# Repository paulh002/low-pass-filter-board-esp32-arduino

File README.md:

# low-pass-filter-board-esp32-arduino
Lowpass filter board managed by ESP32

Low pass filter for RF amp managed by ESP32 VFO or RF Amp / SWR meter (also ESP32).
I use the same PCB as the VFO as controler but do not install the VFO components like si5351. The LPF can be direct managed from VFO software or stand alone with SWR / RFAMP software, from Loftur Jonasson, TF3LJ / VE2LJX (PSWR_T software). I made an adaption of this software for ESP32 and Adafruit 2.8 display. But I am not completly happy with it. Because it uses fixed spaced fonts which are not available in adafruit library. But for now it works with some GUI bugs which I still need to fix.

Here the LPF build in into my tranceiver and managed by esp32 VFO.

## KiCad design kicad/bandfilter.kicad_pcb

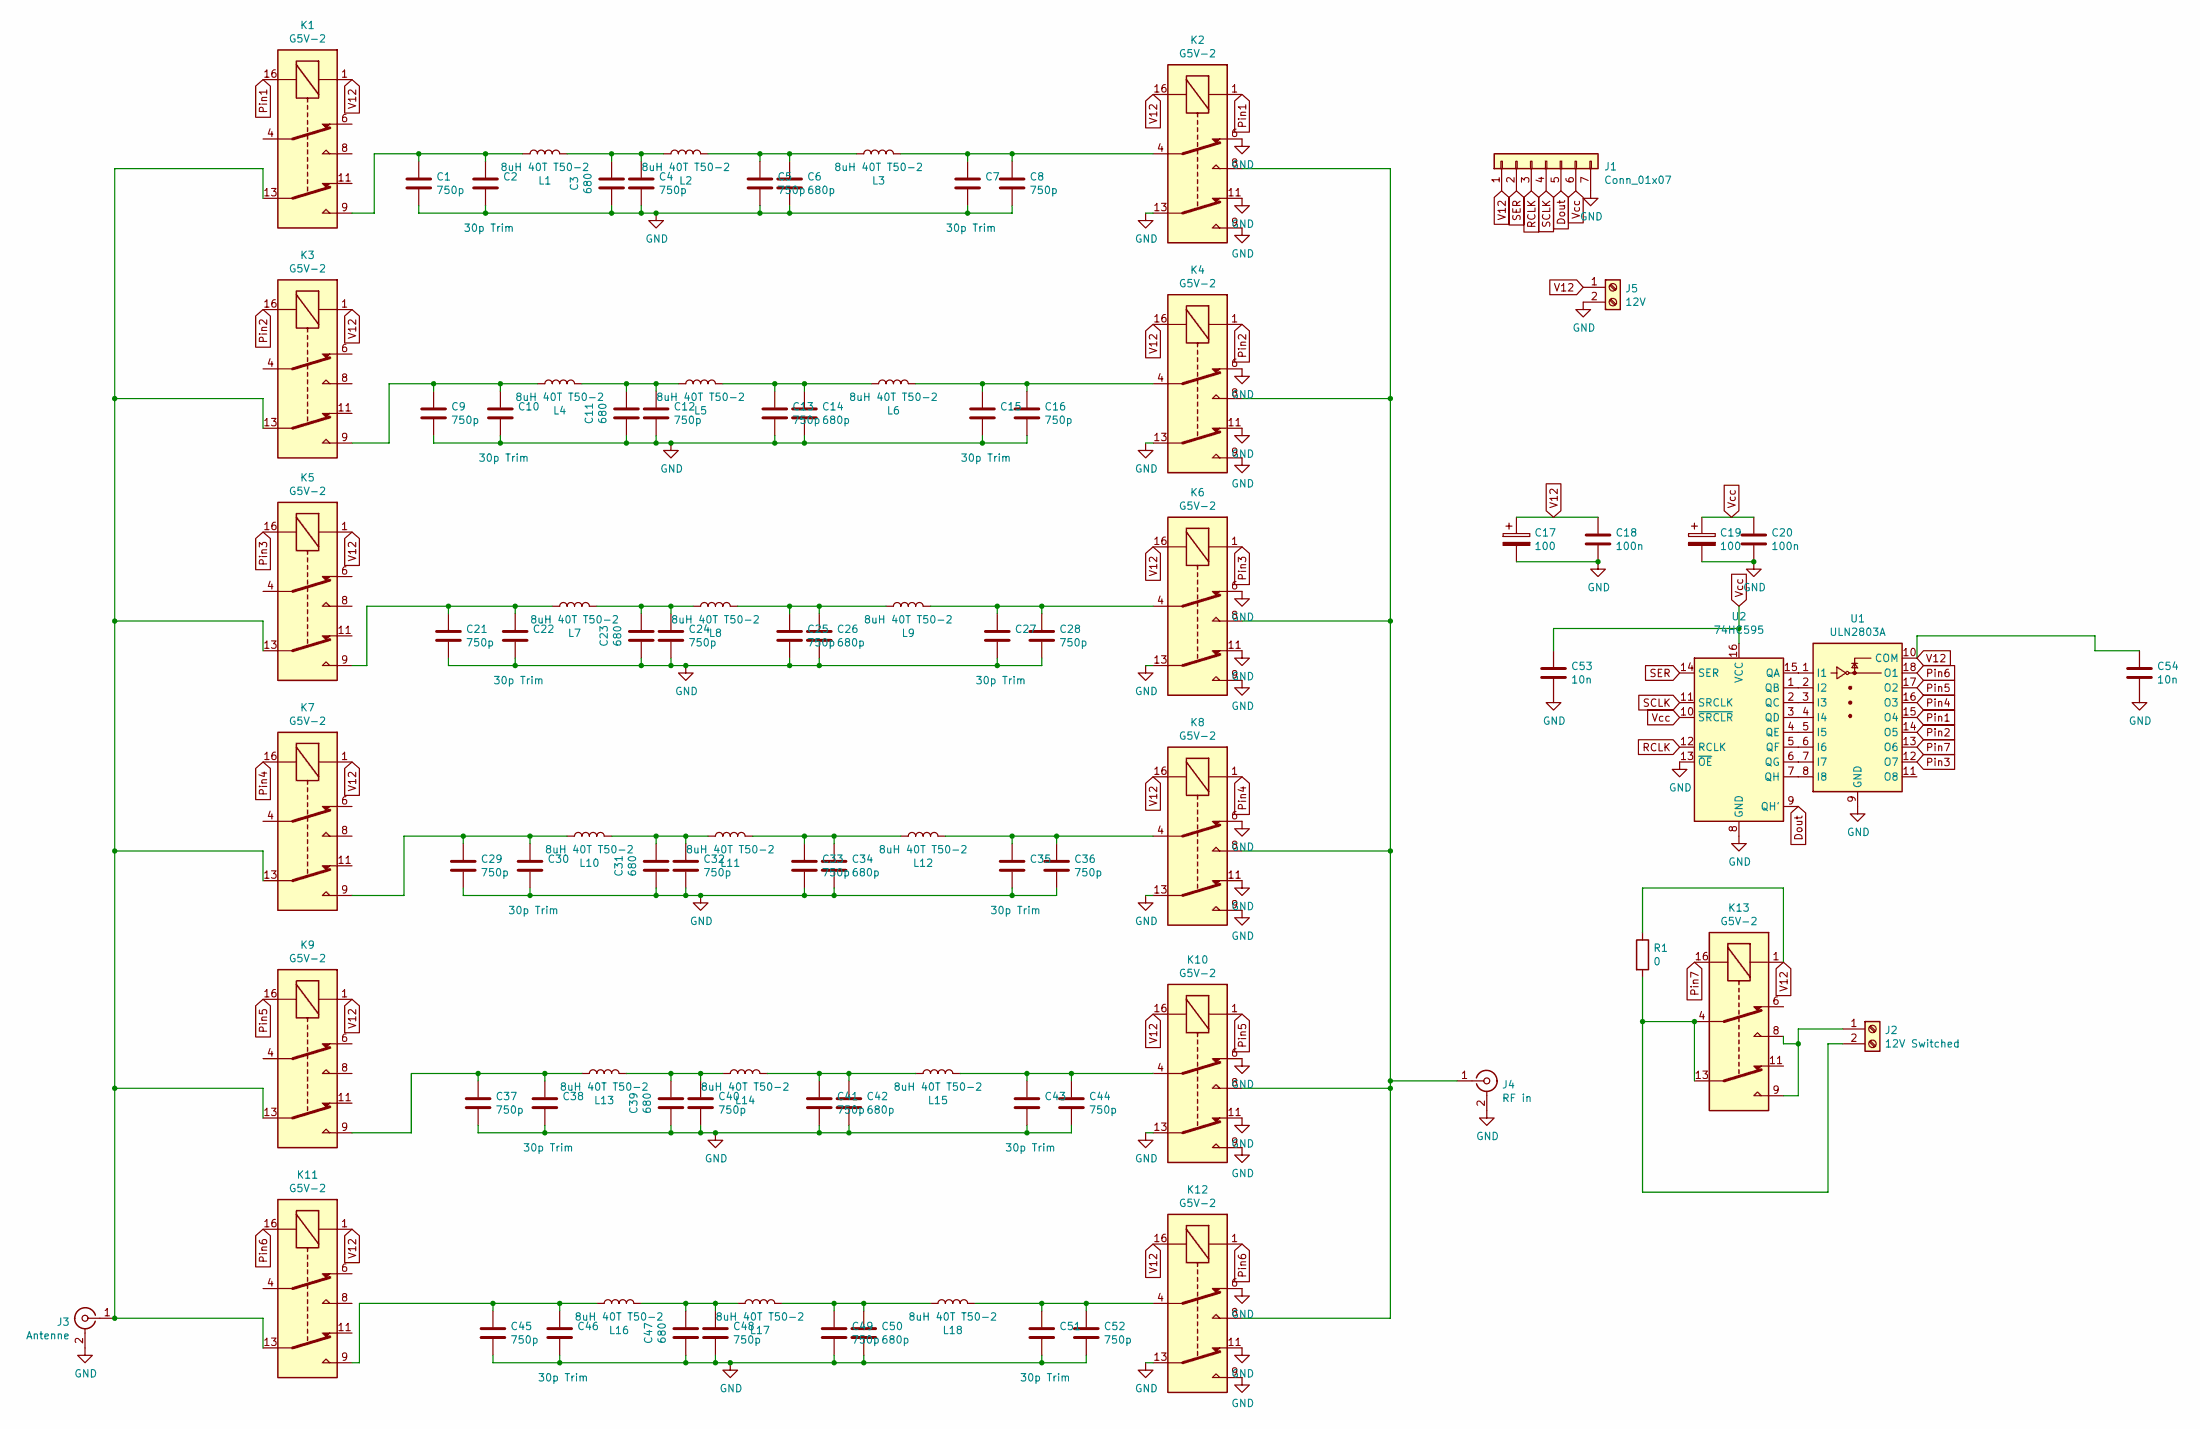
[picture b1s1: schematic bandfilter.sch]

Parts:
C1, C4, C5, C8, C9, C12, C13, C16, C21, C24, C25, C28, C29, C32, C33, C36, C37, C40, C41, C44, C45, C48, C49, C52: 750p; C_Disc_D9.0mm_W5.0mm_P5.00mm
C2, C7, C10, C15, C22, C27, C30, C35, C38, C43, C46, C51: 30p Trim; C_Disc_D9.0mm_W5.0mm_P5.00mm
C3, C11, C23, C31, C39, C47: 680; C_Disc_D9.0mm_W5.0mm_P5.00mm
C6, C14, C26, C34, C42, C50: 680p; C_Disc_D9.0mm_W5.0mm_P5.00mm
C17, C19: 100; CP_Radial_D8.0mm_P5.00mm
C18, C20: 100n; C_Disc_D9.0mm_W5.0mm_P5.00mm
C53, C54: 10n; C_Disc_D9.0mm_W5.0mm_P5.00mm
J1: Conn_01x07; PinSocket_1x07_P2.54mm_Vertical
J2: 12V Switched; TerminalBlock_MetzConnect_Type011_RT05502HBWC_1x02_P5.00mm_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
J3: Antenne; SMA_Amphenol_132134_Vertical
J4: RF in; SMA_Amphenol_132134_Vertical
J5: 12V; TerminalBlock_MetzConnect_Type011_RT05502HBWC_1x02_P5.00mm_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
K1, K2, K3, K4, K5, K6, K7, K8, K9, K10, K11, K12, K13: G5V-2; Relay_DPDT_Omron_G5V-2
L1, L2, L3, L4, L5, L6, L7, L8, L9, L10, L11, L12, L13, L14, L15, L16, L17, L18: 8uH 40T T50-2; Transformer_Toroid_Horizontal_D14.0mm_Amidon-T50
R1: 0; R_Axial_DIN0204_L3.6mm_D1.6mm_P2.54mm_Vertical
U1: ULN2803A; DIP-18_W7.62mm
U2: 74HC595; DIP-16_W7.62mm_LongPads

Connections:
Dout: J1.5, U2.9 (QH')
GND: C1.1, C2.1, C3.2, C4.1, C5.1, C6.1, C7.1, C8.1, C9.1, C10.1, C11.2, C12.1, C13.1, C14.1, C15.1, C16.1, C17.2, C18.1, C19.2, C20.1, C21.1, C22.1, C23.2, C24.1, C25.1, C26.1, C27.1, C28.1, C29.1, C30.1, C31.2, C32.1, C33.1, C34.1, C35.1, C36.1, C37.1, C38.1, C39.2, C40.1, C41.1, C42.1, C43.1, C44.1, C45.1, C46.1, C47.2, C48.1, C49.1, C50.1, C51.1, C52.1, C53.1, C54.1, J1.7, J3.2 (Ext), J4.2 (Ext), J5.2, K2.6, K2.9, K2.11, K2.13, K4.6, K4.9, K4.11, K4.13, K6.6, K6.9, K6.11, K6.13, K8.6, K8.9, K8.11, K8.13, K10.6, K10.9, K10.11, K10.13, K12.6, K12.9, K12.11, K12.13, U1.9 (GND), U2.8 (GND), U2.13 (~OE)
unnamed: C1.2, C2.2, K1.9, L1.1
unnamed: C3.1, C4.2, L1.2, L2.1
unnamed: C5.2, C6.2, L2.2, L3.1
unnamed: C7.2, C8.2, K2.4, L3.2
unnamed: C9.2, C10.2, K3.9, L4.1
unnamed: C11.1, C12.2, L4.2, L5.1
unnamed: C13.2, C14.2, L5.2, L6.1
unnamed: C15.2, C16.2, K4.4, L6.2
unnamed: C21.2, C22.2, K5.9, L7.1
unnamed: C23.1, C24.2, L7.2, L8.1
unnamed: C25.2, C26.2, L8.2, L9.1
unnamed: C27.2, C28.2, K6.4, L9.2
unnamed: C29.2, C30.2, K7.9, L10.1
unnamed: C31.1, C32.2, L10.2, L11.1
unnamed: C33.2, C34.2, L11.2, L12.1
unnamed: C35.2, C36.2, K8.4, L12.2
unnamed: C37.2, C38.2, K9.9, L13.1
unnamed: C39.1, C40.2, L13.2, L14.1
unnamed: C41.2, C42.2, L14.2, L15.1
unnamed: C43.2, C44.2, K10.4, L15.2
unnamed: C45.2, C46.2, K11.9, L16.1
unnamed: C47.1, C48.2, L16.2, L17.1
unnamed: C49.2, C50.2, L17.2, L18.1
unnamed: C51.2, C52.2, K12.4, L18.2
unnamed: J2.1, K13.8, K13.9
unnamed: J2.2, K13.4, K13.13, R1.2
unnamed: J3.1 (In), K1.13, K3.13, K5.13, K7.13, K9.13, K11.13
unnamed: J4.1 (In), K2.8, K4.8, K6.8, K8.8, K10.8, K12.8
unnamed: U1.1 (I1), U2.15 (QA)
unnamed: U1.2 (I2), U2.1 (QB)
unnamed: U1.3 (I3), U2.2 (QC)
unnamed: U1.4 (I4), U2.3 (QD)
unnamed: U1.5 (I5), U2.4 (QE)
unnamed: U1.6 (I6), U2.5 (QF)
unnamed: U1.7 (I7), U2.6 (QG)
unnamed: U1.8 (I8), U2.7 (QH)
Pin1: K1.16, K2.1, U1.15 (O4)
Pin2: K3.16, K4.1, U1.14 (O5)
Pin3: K5.16, K6.1, U1.12 (O7)
Pin4: K7.16, K8.1, U1.16 (O3)
Pin5: K9.16, K10.1, U1.17 (O2)
Pin6: K11.16, K12.1, U1.18 (O1)
Pin7: K13.16, U1.13 (O6)
RCLK: J1.3, U2.12 (RCLK)
SCLK: J1.4, U2.11 (SRCLK)
SER: J1.2, U2.14 (SER)
V12: C17.1, C18.2, C54.2, J1.1, J5.1, K1.1, K2.16, K3.1, K4.16, K5.1, K6.16, K7.1, K8.16, K9.1, K10.16, K11.1, K12.16, K13.1, R1.1, U1.10 (COM)
Vcc: C19.1, C20.2, C53.2, J1.6, U2.10 (~SRCLR), U2.16 (VCC)

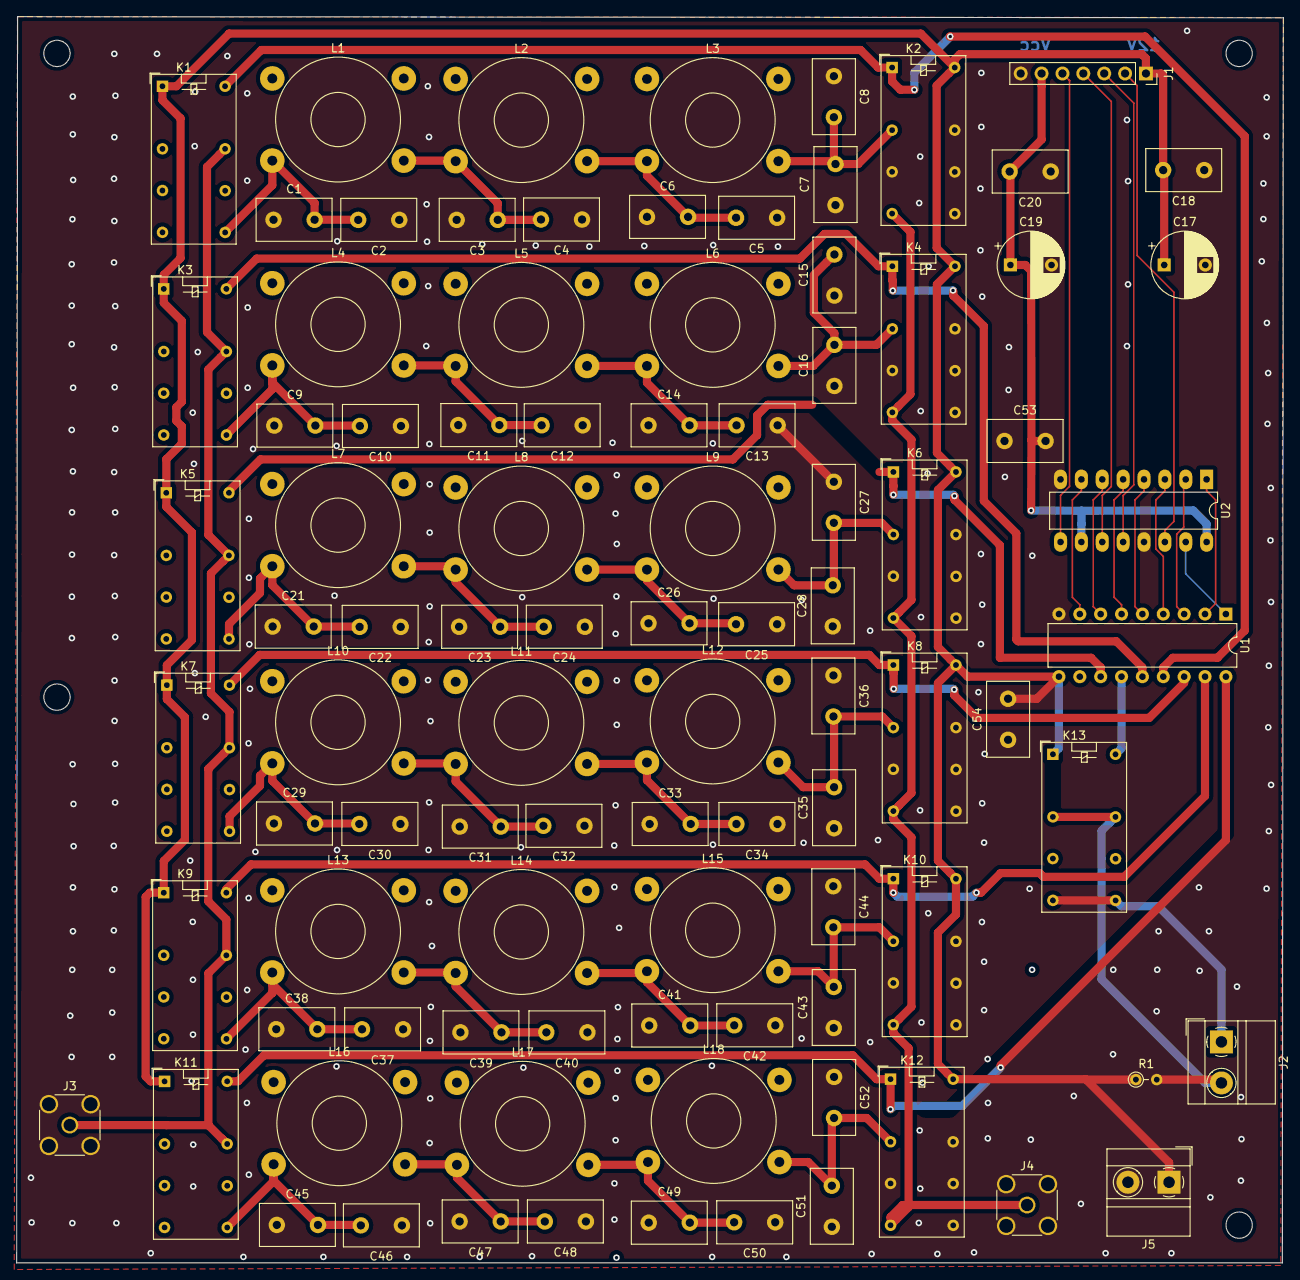
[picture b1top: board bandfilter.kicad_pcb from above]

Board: 2 copper layers, 154.2 x 151.7 mm, 97 parts (0 on the bottom side), 50 nets.

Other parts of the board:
 : MountingHole_3.2mm_M3
 #2,  #3,  #4: MountingHole_3.2mm_M3

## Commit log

2020-10-26 files
